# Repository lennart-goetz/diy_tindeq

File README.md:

# DIY Tindeq
When training for climbing, you will come across some specialzied training tools. 

Some measure the force the climber can pull on a ledge, and visualize them on a phone. 
Those devices are quite expensive, so this is my try to build my own. 

This project is based on a crane-scale to get the strain gauge. 
To measure the small Voltage across it, the HX711 IC is used. To visualize and process
the data, I use a ESP32 S3. I went for S3 because it can be programmed directly via usb, without the need for additional usb-serial adapters. 

In the current Version (V1) There are 4 pads on the left, that are connected to the strain gauge. 
On the right side, there are 4 pads for power supply. V-bus and b-gnd are 5V and gnd from the usb port. They will be connected to external Battery management system. The output of the external Battery mangement System will be connected to OUT+ and OUT- 

The pcb is designed to support charging via USB and programming via usb. 
I am using a TP4056 Module for Managing the single cell Lithium batterie. Make sure your BMS support overdischarge protection and overcharging protection. 

The pcb is not tested yet, I will probably continue updating this repo after testing. 

## Update 16.03.26

I assembled the PCB and did some testing. Soldering the mcp1727 is quite tricky. I ended up putting some soldern on the pads with a soldering iron, then adding flux and heating up the whole area with a hot air gun. 
Ideally I would recommend using a different package LDO. (maybe the 1727 even exists in a better package?)

The other components are fine with some experience in SMD soldering.

Flashing the software to the ESP32 S3 was not trivial. I used the wrong configuration (wrong flash size selected). After that the ESP ended up in a boot cycle. I had to manually bridge the boot en EN pin to bring it back into bootload mode. 

## Update 26.03.26

After some more testing it was obvious that the sensor readings were very noisy. However the issue was quite easy to fix. In the inital build of the prototype I fixed the wires from the sensor to the pcb with hot glue. That formed a loop together with the alloy. The Wifi Antenna of the ESP induced voltages into that loop, which ruined the sensor readings. After removing the hot glue and running the wires further away from the antenna, the measurements were fine. 

## Update 14.04.26
In the last month I used the prototype a bit, and I was quite happy with the way it worked. So I decided to design my first 3D case and try to print it. I was surprised how easy it was to learn, and I can definitely recommend! That is one evening well invested in my opinion. To get started I can recommend Tinkercad. It is a browser based 3D modeling software with very limited features but totally powerful enough for what I am doing. The next day I was able to print it in my local makerspace and place all the components in the case.

In this photo you can see an issue that I encountered. While testing to prototype, I hot glued the wires from the strain gauge to the pcb. This turned out to be a problem because the hot glue was a little bit too hot and held on to the pcb too well. When I tried to remove it, one of the soldering pads ripped off the pcb. I found a different place to solder the wire to (Capacitor 9) but that Capacitor is a bit far away from the soldering pad for gnd. That opens up a "loop" between ground and VCC, which results in a very noisy signal.

However the solution was equally easy and elegant. As you can see the red and the black wire form a loop, cross and then go to their soldering pads. So in total there are two loops. Those have approximately the same size, but a different orientation. Therefore the induced voltages cancel out quite nicely. 

After I tested the functions of the board one last time, I glued the lid to the case.

## Lessons Learned

 - use bigger package for MCP1727 or order a stencil to reflow solder the pcb
 - install some Status leds for the ESP
 - install some power LED for the board
 - include the BMS on the pcb for the next rev of the board
 - The micro USB plug has the wrong footprint. need to fix that!
 - maybe put some thought into the form factor next time
 - the esp32 pins closest to the antenna are quite hard to solder, if the solder tip is too small

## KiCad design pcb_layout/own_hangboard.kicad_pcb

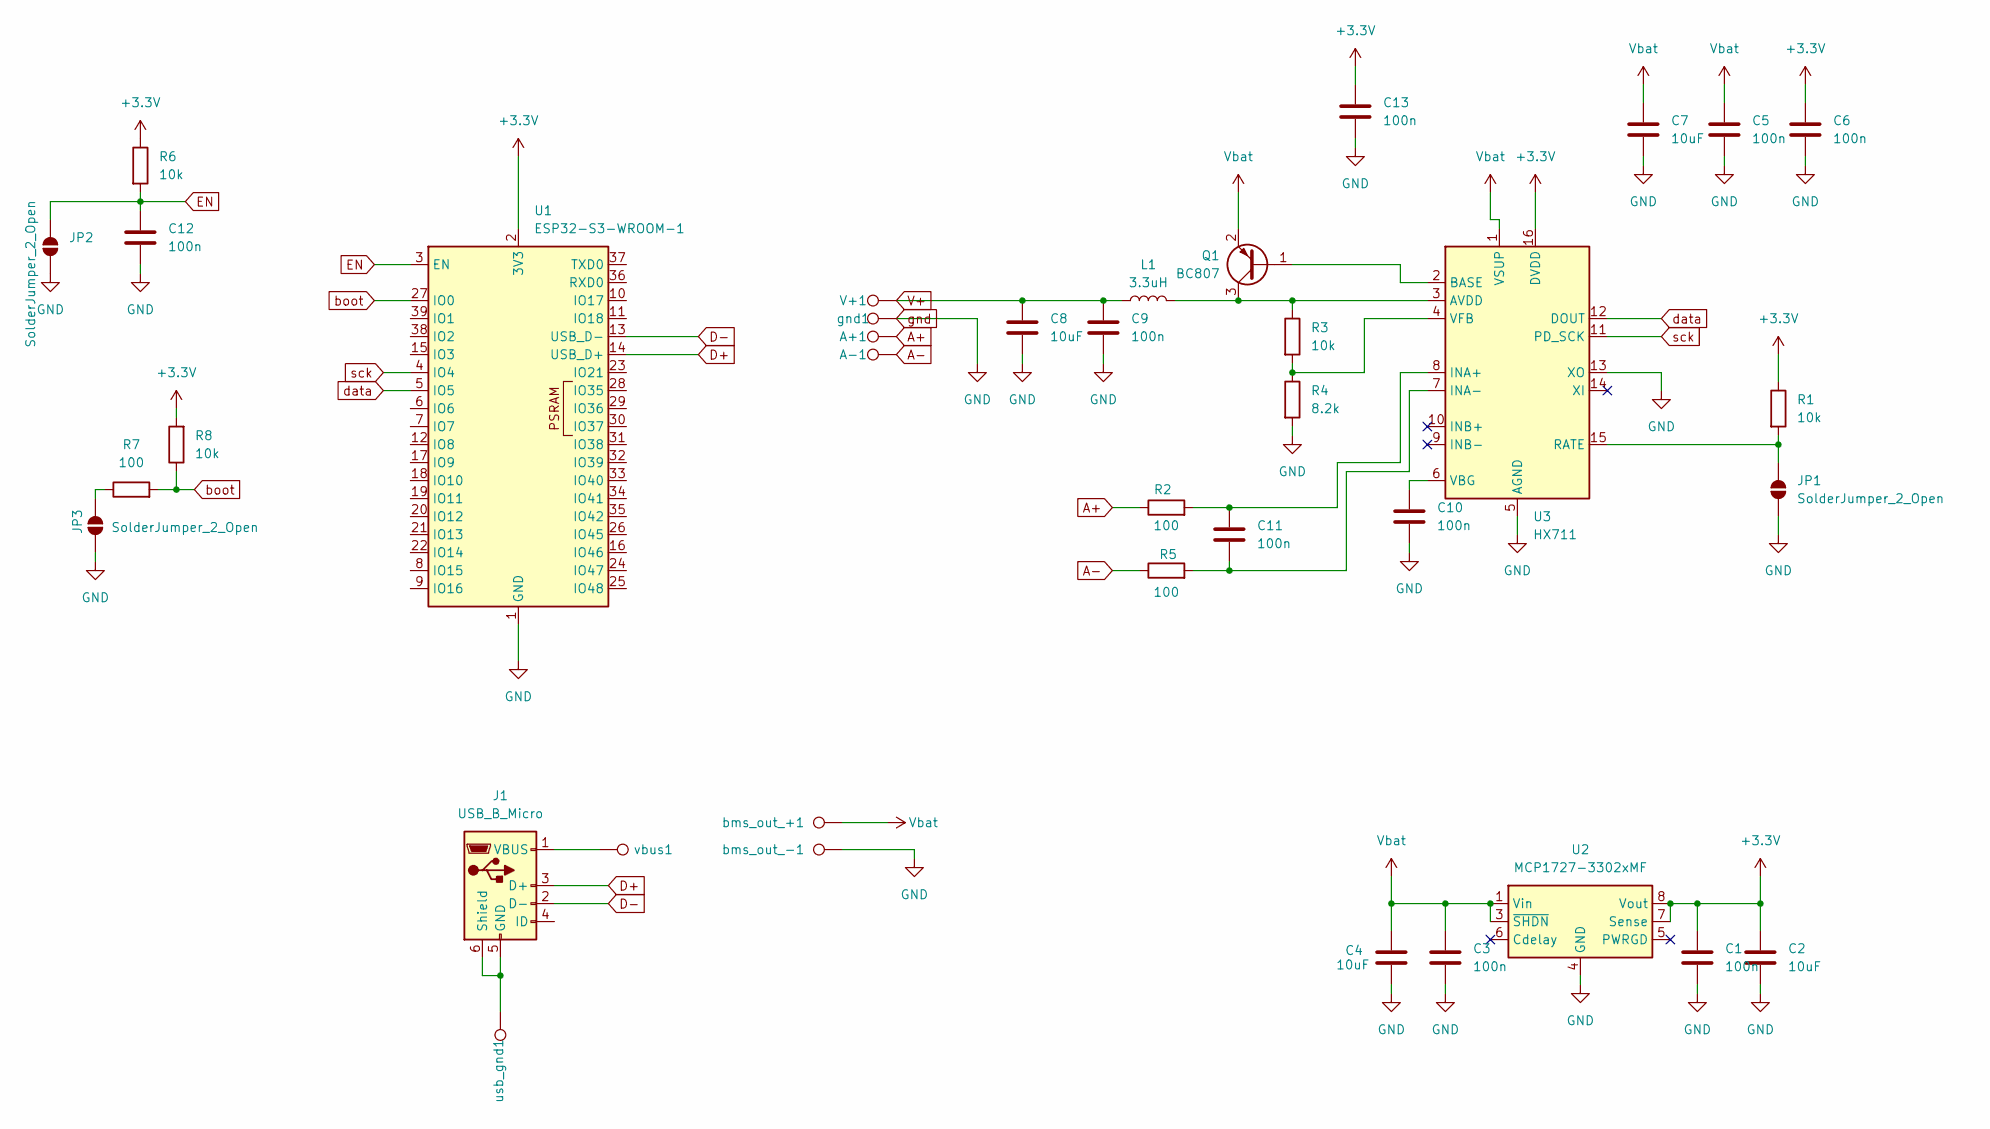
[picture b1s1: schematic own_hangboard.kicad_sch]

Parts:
A+1: TestPoint; TestPoint_Pad_2.0x2.0mm
A-1: TestPoint; TestPoint_Pad_2.0x2.0mm
C1, C3, C5, C6, C9, C10, C11, C12, C13: 100n; C_0805_2012Metric
C2, C4, C7, C8: 10uF; C_1206_3216Metric
J1: USB_B_Micro; USB_Micro-B_Wuerth_629105150521
JP1, JP2, JP3: SolderJumper_2_Open; SolderJumper-2_P1.3mm_Open_RoundedPad1.0x1.5mm
L1: 3.3uH; C_1206_3216Metric
Q1: BC807; SOT-23
R1, R3, R6, R8: 10k; C_0805_2012Metric
R2, R5, R7: 100; C_0805_2012Metric
R4: 8.2k; C_0805_2012Metric
U1: ESP32-S3-WROOM-1
U2: MCP1727-3302xMF; DFN-8-1EP_3x3mm_P0.65mm_EP1.55x2.4mm
U3: HX711; SOIC-16_3.9x9.9mm_P1.27mm
V+1: TestPoint; TestPoint_Pad_2.0x2.0mm
bms_out_+1: TestPoint; TestPoint_Pad_2.0x2.0mm
bms_out_-1: TestPoint; TestPoint_Pad_2.0x2.0mm
gnd1: TestPoint; TestPoint_Pad_2.0x2.0mm
usb_gnd1: TestPoint; TestPoint_Pad_2.0x2.0mm
vbus1: TestPoint; TestPoint_Pad_2.0x2.0mm

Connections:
+3.3V: C1.1, C2.1, C6.1, C13.1, R1.1, R6.1, R8.2, U1.2 (3V3), U2.7 (Sense), U2.8 (Vout), U3.16 (DVDD)
A+: A+1.1, R2.1
A-: A-1.1, R5.1
D+: J1.3 (D+), U1.14 (USB_D+)
D-: J1.2 (D-), U1.13 (USB_D-)
EN: C12.1, JP2.2 (B), R6.2, U1.3 (EN)
unnamed: J1.5 (GND), J1.6 (Shield), usb_gnd1.1
unnamed: J1.1 (VBUS), vbus1.1
unnamed: JP1.2 (B), R1.2, U3.15 (RATE)
unnamed: JP3.1 (A), R7.1
unnamed: Q1.1 (B), U3.2 (BASE)
unnamed: L1.2, Q1.3 (C), R3.1, U3.3 (AVDD)
unnamed: C11.1, R2.2, U3.8 (INA+)
unnamed: C11.2, R5.2, U3.7 (INA-)
unnamed: C10.1, U3.6 (VBG)
unnamed: R3.2, R4.1, U3.4 (VFB)
V+: C8.1, C9.1, L1.1, V+1.1
Vbat: C3.1, C4.1, C5.1, C7.1, Q1.2 (E), U2.1 (Vin), U2.2 (Vin), U2.3 (~SHDN), U3.1 (VSUP), bms_out_+1.1
boot: R7.2, R8.1, U1.27 (IO0)
data: U1.5 (IO5), U3.12 (DOUT)
gnd: C1.2, C2.2, C3.2, C4.2, C5.2, C6.2, C7.2, C8.2, C9.2, C10.2, C12.2, C13.2, JP1.1 (A), JP2.1 (A), JP3.2 (B), R4.2, U1.1 (GND), U1.40 (GND), U1.41 (GND), U2.4 (GND), U2.9 (GND), U3.5 (AGND), U3.13 (XO), bms_out_-1.1, gnd1.1
sck: U1.4 (IO4), U3.11 (PD_SCK)

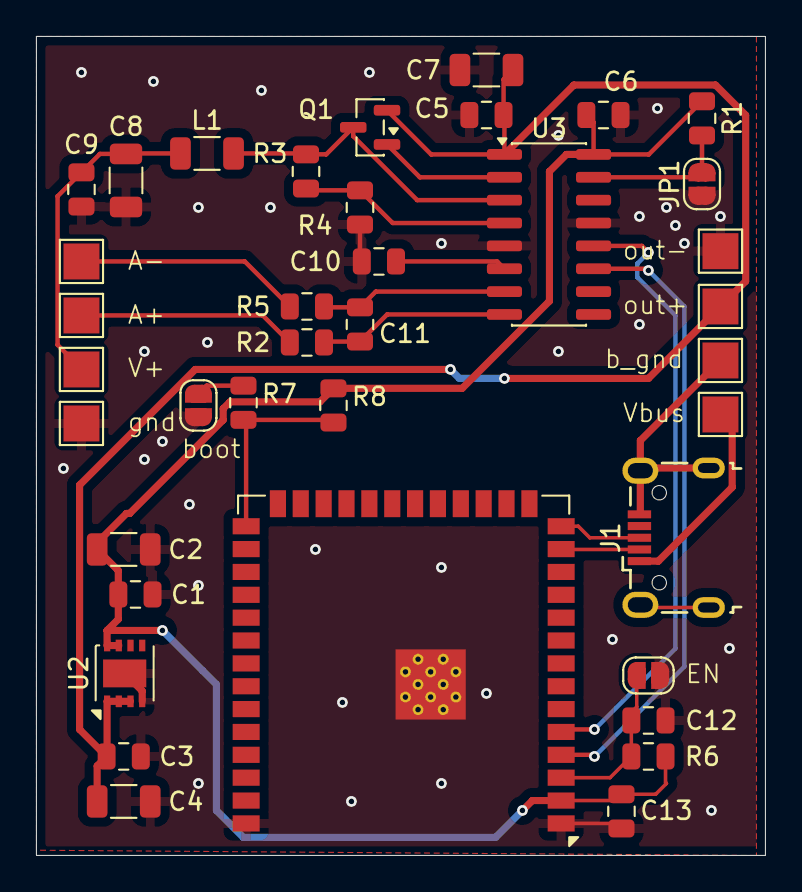
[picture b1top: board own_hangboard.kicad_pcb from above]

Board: 2 copper layers, 40.5 x 45.5 mm, 38 parts (0 on the bottom side), 22 nets.

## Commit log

2026-03-07 initial commit: Version 1 des pcb design und erster vibe code
2026-03-07 added a README
2026-03-16 assembled the PCB V1
2026-03-16 typo
2026-03-24 new code
2026-03-26 updates Readme
2026-04-14 added stl 3D File
2026-04-14 changed photos
